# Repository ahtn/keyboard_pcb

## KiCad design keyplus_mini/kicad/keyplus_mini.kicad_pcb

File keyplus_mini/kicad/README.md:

# keyplus mini PCB

## Firmware

[See here](https://github.com/ahtn/keyplus)

## License

[CC-BY-SA](https://creativecommons.org/licenses/by-sa/4.0/)

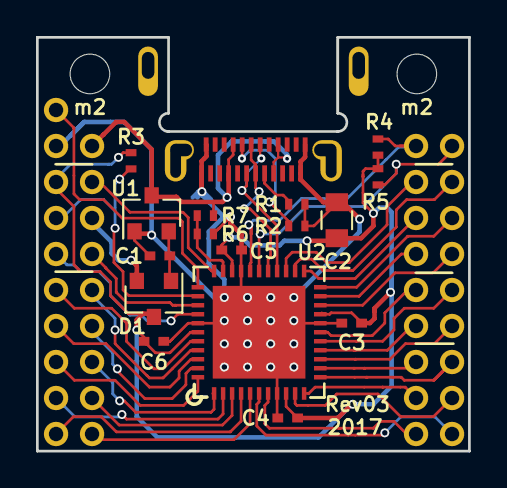
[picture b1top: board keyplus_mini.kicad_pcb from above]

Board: 2 copper layers, 24.0 x 23.0 mm, 20 parts (0 on the bottom side), 43 nets.

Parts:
C1: 1uF; C_0402_NoSilk
C2: 10uF; C_0805
C3, C4, C5, C6: 0.1uF; C_0402_NoSilk
D1: D_Schottky_x2_KCom_AAK; SOT-23
J1: USB_TYPE_C; DX07B024JJ1R1300
J2, J4: Conn_02x09_Odd_Even; Pin_Header_Straight_2x09_Pitch2.00mm_No_Silk
J3: CONN_01X01; Pin_Header_Straight_1x01_Pitch2.00mm_No_Silk
R1, R2: 5.1k; R_0402_NoSilk
R3, R4, R5: 10k; R_0402_NoSilk
R6, R7: 100k; R_0402_NoSilk
U1: MCP1700-3302E_SOT23; SOT-23
U2: ATXMEGA16A4U-MH_EPAD; QFN-44-1EP_7x7mm_Pitch0.5mm_Alt_Silk

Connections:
+3V3: C2.2, C3.2, C4.2, C5.2, C6.2, D1.3, J2.3, R3.1, R4.1, R5.1, U2.9, U2.19, U2.31, U2.39
+5V: J1.A4, J1.A9, J1.B4, J1.B9, J2.2, R6.1, U1.3
+BATT: D1.2, J2.6
/D+: J1.A6, J1.B6, U2.27
/D-: J1.A7, J1.B7, U2.26
/PA0: J2.9, U2.40
/PA1: J2.10, U2.41
/PA2: J2.11, U2.42
/PA3: J2.12, U2.43
/PA4: J2.13, U2.44
/PA5: J2.14, U2.1
/PA6: J2.15, U2.2
/PA7: J2.16, U2.3
/PB0: J2.17, U2.4
/PB1: J2.18, U2.5
/PB2: J4.18, U2.6
/PB3: J4.17, U2.7
/PC0: J4.16, U2.10
/PC1: J4.15, U2.11
/PC2: J4.14, U2.12
/PC3: J4.13, U2.13
/PC4: J4.12, U2.14
/PC5: J4.11, U2.15
/PC6: J4.10, U2.16
/PC7: J4.9, U2.17
/PCL: J2.5, R3.2, U2.35
/PD0: J4.8, U2.20
/PD1: J4.7, U2.21
/PD2: J4.6, U2.22
/PD3: J4.5, U2.23
/PD4: J4.4, U2.24
/PD5: J4.3, U2.25
/PDI: J3.1, U2.34
/PE0: J4.2, R5.2, U2.28
/PE1: J4.1, R4.2, U2.29
/PE3: J2.4, U2.33
/PR0: J2.8, U2.36
/PR1: J2.7, U2.37
GND: C1.1, C2.1, C3.1, C4.1, C5.1, C6.1, J1.A1, J1.A12, J1.B1, J1.B12, J2.1, R1.2, R2.2, R7.2, U1.1, U2.8, U2.18, U2.30, U2.38, U2.45
unnamed: C1.2, D1.1, U1.2
unnamed: J1.A5, R1.1
unnamed: J1.B5, R2.1
unnamed: R6.2, R7.1, U2.32

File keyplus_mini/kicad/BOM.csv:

Designator,Part,Value,Quantity,URL,Datasheet,Alternatives
"R1, R2",,5.1k,2,https://www.digikey.com/product-detail/en/yageo/RC0402FR-075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,,
"R3, R4, R5",,10k,3,https://www.digikey.com/product-detail/en/yageo/RC0402JR-071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,,
"R6, R7",,100k,2,https://www.digikey.com/product-detail/en/yageo/RC0402FR-071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,,
C1,,1uF,1,https://www.digikey.com/product-detail/en/murata-electronics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,,
C2,,10uF,1,https://www.digikey.com/product-detail/en/murata-electronics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,http://psearch.en.murata.com/capacitor/product/GRM21BR61C106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,
"C3, C4, C5, C6",,0.1uF,4,https://www.digikey.com/product-detail/en/murata-electronics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,,
D1,BAT54C,Common cathode diode array,1,https://www.digikey.com/product-detail/en/diodes-incorporate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,https://www.diodes.com/assets/Datasheets/ds11005.pdf,
U1,MCP1700,3.3V regulator,1,https://www.digikey.com/product-detail/en/microchip-technolo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,http://ww1.microchip.com/downloads/en/DeviceDoc/20001826D.pdf,
U2,Atxmega32A4U,,1,https://www.digikey.com/product-detail/en/microchip-technolo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,http://www.atmel.com/images/Atmel-8387-8-and16-bit-AVR-Micro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,"ATxmega64A4U, Atxmega128A4U"
J1,DX07B024JJ2R1500,,1,https://www.digikey.com/product-detail/en/jae-electronics/DX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,,DX07B024JJ1R1500

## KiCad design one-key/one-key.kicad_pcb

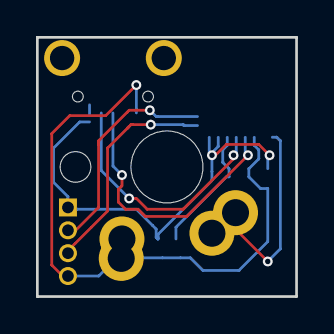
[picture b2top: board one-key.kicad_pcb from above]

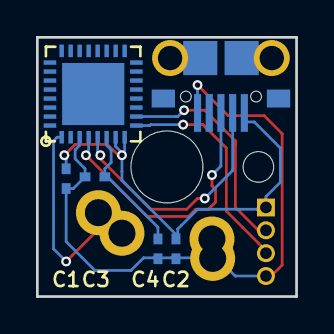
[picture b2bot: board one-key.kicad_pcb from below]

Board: 2 copper layers, 14.4 x 14.4 mm, 8 parts (8 on the bottom side), 8 nets.

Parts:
C1, C3: 0.1uF; C_0402_NoSilk
C2, C4: 1uF; C_0402_NoSilk
J1: USB_OTG; micro_usb_no_silk
J2: Conn_01x04; Pin_Header_Angled_1x04_Pitch1.27mm_no_silk
SW1: SW_Push; Cherry_MX_Matias_No_Silk_Border
U1: C8051F38x_32; QFN-32-1EP_5x5mm_Pitch0.5mm

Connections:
+3V3: C3.1, C4.1, U1.6
+5V: C1.1, C2.1, J1.1, J2.1, U1.7, U1.8
GND: C1.2, C2.2, C3.2, C4.2, J1.5, J2.4, SW1.1, U1.3
unnamed: J1.2, U1.5
unnamed: J1.3, U1.4
unnamed: J2.2, U1.10
unnamed: J2.3, U1.9
unnamed: SW1.2, U1.1
